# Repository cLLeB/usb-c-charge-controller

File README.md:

# ESP32-C3 smart USB-C charge controller

A small adapter that sits between a USB-C charger and a phone and stops charging at a battery level you choose, for example 80 %, then starts again at a lower one, for example 40 %. The phone reports its battery level over Wi-Fi, and the adapter does the switching. I designed the circuit and the board, wrote the firmware and the companion apps, and assembled, soldered and tested it in October 2026.

## How it works

To the charger the adapter looks like a simple 5 V device, and to the phone it looks like a simple 5 V charger. Stopping the charge is the same as pulling the plug out, so every phone already knows how to handle it.

- **Power path.** A P channel MOSFET (SI4435) switches the 5 V VBUS line, driven through a 2N7000 by the ESP32-C3. Up to 3 A at 5 V, nothing above 5 V anywhere on the board.
- **USB-C signalling.** The firmware reads the charger's CC pins to learn whether it offers basic current, 1.5 A or 3 A, then advertises the matching limit to the phone by switching one of three CC resistors.
- **Phone detection.** An analog input on the phone side CC line tells the controller whether something is plugged in, even while the output is off.
- **State.** The allowed or stopped state is kept in flash, so it survives a restart. A red LED shows the state, and the BOOT button gives "charge to 100 % once", WPS pairing and a reset.

The full circuit table, pin map and decision rules are in [DESIGN.md](DESIGN.md).

## Firmware

C++ for the Seeed XIAO ESP32-C3 in the Arduino environment ([`firmware/smart_socket/`](firmware/smart_socket)).

- Wireless control over Wi-Fi, with a web page served by the adapter and a JSON API.
- Setup over Bluetooth from the Android app, by WPS, or through a setup network.
- Firmware updates over the air, through Wi-Fi or Bluetooth, with an MD5 check before restarting into the new program.
- Each adapter answers at its own `smartsocket-xxxxxx.local` address, so several can share one network.
- Upper and lower limits, a charge timer, charging hours, a heat cut out and the last 20 charging runs.

The decision rules are mirrored in Python in [`tools/logic.py`](tools/logic.py) and covered by 62 scenario tests. [`tools/test_device.py`](tools/test_device.py) checks a real adapter feature by feature over Wi-Fi.

Before building, copy `firmware/smart_socket/secrets.example.h` to `secrets.h` and set your own update password.

## Apps

- **Android** ([`app-android/`](app-android)): finds every adapter on the network, sets one up over Bluetooth, and reports the phone's battery level in the background.
- **Windows** ([`app-windows/`](app-windows)): every adapter in one list with limits, timer, history and program upload.
- **iPhone**: two Shortcuts automations calling `http://smartsocket.local/api/battery?level=…`, described in [PHONE-SETUP.md](PHONE-SETUP.md).

## Board

Rev 0.2, 51.2 x 24 mm, two layers, made by PCBWay. The charger plugs into one end and the phone cable leaves from the other. Schematic and board are generated by scripts in [`kicad/`](kicad) and checked with ERC, DRC and a netlist comparison.

| | |
|---|---|
|  |  |
|  |  |

A 3D printed case is drafted in OpenSCAD in [`case/`](case).

## Limits of version 1

- 5 V only, up to 15 W. Laptops need 20 V and USB Power Delivery negotiation, which is a job for version 2.
- Charge only: the data wires are not connected.
- Needs a charger with a USB-C socket.

## Tools

ESP32-C3, C++, KiCad, Python, Java for Android, C# for Windows, OpenSCAD.

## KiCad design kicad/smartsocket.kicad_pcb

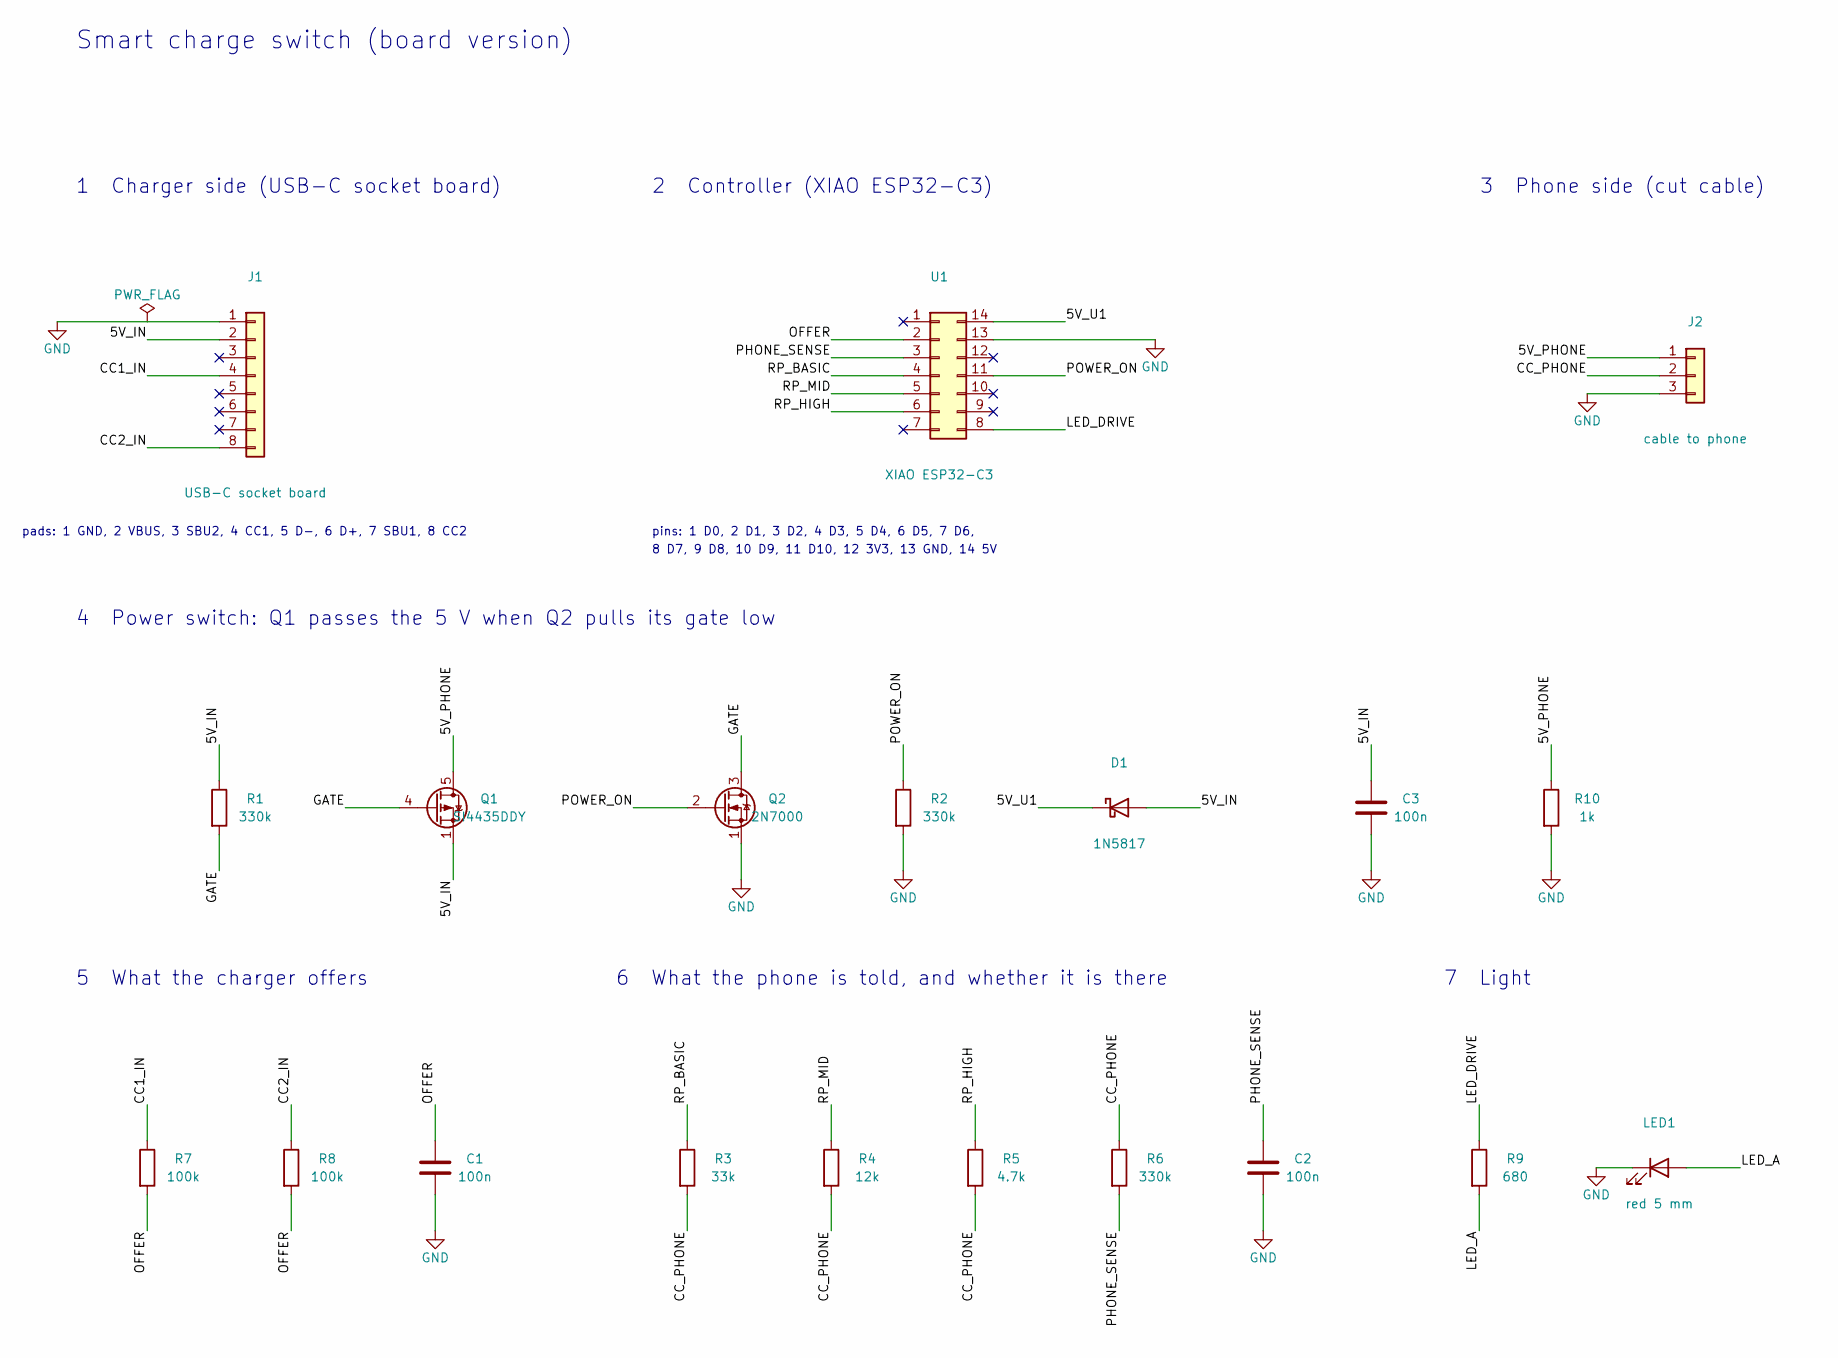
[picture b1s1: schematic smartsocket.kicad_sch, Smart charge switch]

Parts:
C1, C2, C3: 100n; C_Disc_D4.7mm_W2.5mm_P5.00mm
D1: 1N5817; D_DO-41_SOD81_P10.16mm_Horizontal
J1: USB-C socket board; PinHeader_1x08_P2.54mm_Vertical
J2: cable to phone; SolderWire-0.5sqmm_1x03_P4.6mm_D0.9mm_OD2.1mm
LED1: red 5 mm; LED_D5.0mm
Q1: SI4435DDY; SOIC-8_3.9x4.9mm_P1.27mm
Q2: 2N7000; TO-92_Inline_Wide
R1, R2, R6: 330k; R_Axial_DIN0207_L6.3mm_D2.5mm_P7.62mm_Horizontal
R3: 33k; R_Axial_DIN0207_L6.3mm_D2.5mm_P7.62mm_Horizontal
R4: 12k; R_Axial_DIN0207_L6.3mm_D2.5mm_P7.62mm_Horizontal
R5: 4.7k; R_Axial_DIN0207_L6.3mm_D2.5mm_P7.62mm_Horizontal
R7, R8: 100k; R_Axial_DIN0207_L6.3mm_D2.5mm_P7.62mm_Horizontal
R9: 680; R_Axial_DIN0207_L6.3mm_D2.5mm_P7.62mm_Horizontal
R10: 1k; R_Axial_DIN0207_L6.3mm_D2.5mm_P7.62mm_Horizontal
U1: XIAO ESP32-C3; DIP-14_W7.62mm

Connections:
/5V_IN: C3.1, D1.2 (A), J1.2, Q1.1 (S), Q1.2 (S), Q1.3 (S), R1.1
/5V_PHONE: J2.1, Q1.5 (D), Q1.6 (D), Q1.7 (D), Q1.8 (D), R10.1
/5V_U1: D1.1 (K), U1.14
/CC1_IN: J1.4, R7.1
/CC2_IN: J1.8, R8.1
/CC_PHONE: J2.2, R3.2, R4.2, R5.2, R6.1
/GATE: Q1.4 (G), Q2.3 (D), R1.2
/LED_A: LED1.2 (A), R9.2
/LED_DRIVE: R9.1, U1.8
/OFFER: C1.1, R7.2, R8.2, U1.2
/PHONE_SENSE: C2.1, R6.2, U1.3
/POWER_ON: Q2.2 (G), R2.1, U1.11
/RP_BASIC: R3.1, U1.4
/RP_HIGH: R5.1, U1.6
/RP_MID: R4.1, U1.5
GND: C1.2, C2.2, C3.2, J1.1, J2.3, LED1.1 (K), Q2.1 (S), R2.2, R10.2, U1.13

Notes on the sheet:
Smart charge switch (board version)
1 Charger side (USB-C socket board)
pads: 1 GND, 2 VBUS, 3 SBU2, 4 CC1, 5 D-, 6 D+, 7 SBU1, 8 CC2
2 Controller (XIAO ESP32-C3)
pins: 1 D0, 2 D1, 3 D2, 4 D3, 5 D4, 6 D5, 7 D6,
8 D7, 9 D8, 10 D9, 11 D10, 12 3V3, 13 GND, 14 5V
3 Phone side (cut cable)
4 Power switch: Q1 passes the 5 V when Q2 pulls its gate low
5 What the charger offers
6 What the phone is told, and whether it is there
7 Light

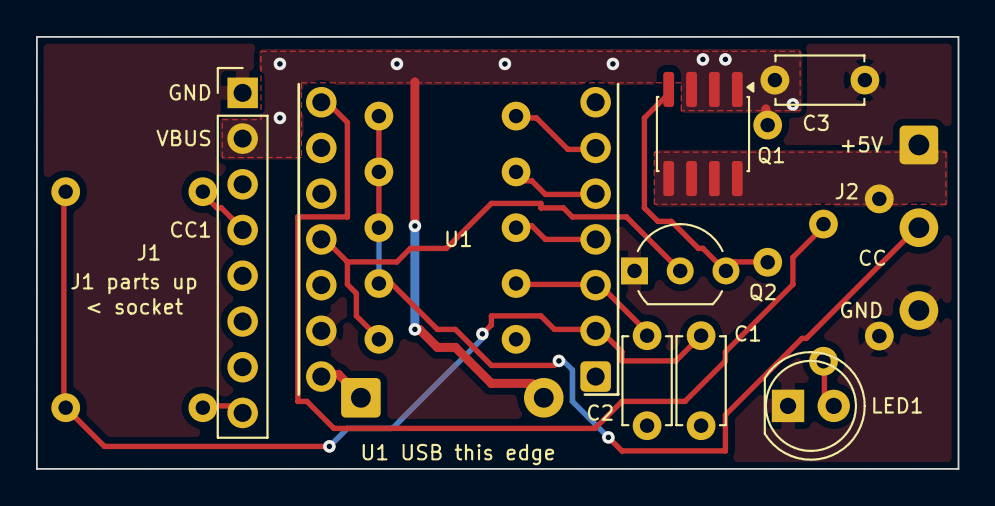
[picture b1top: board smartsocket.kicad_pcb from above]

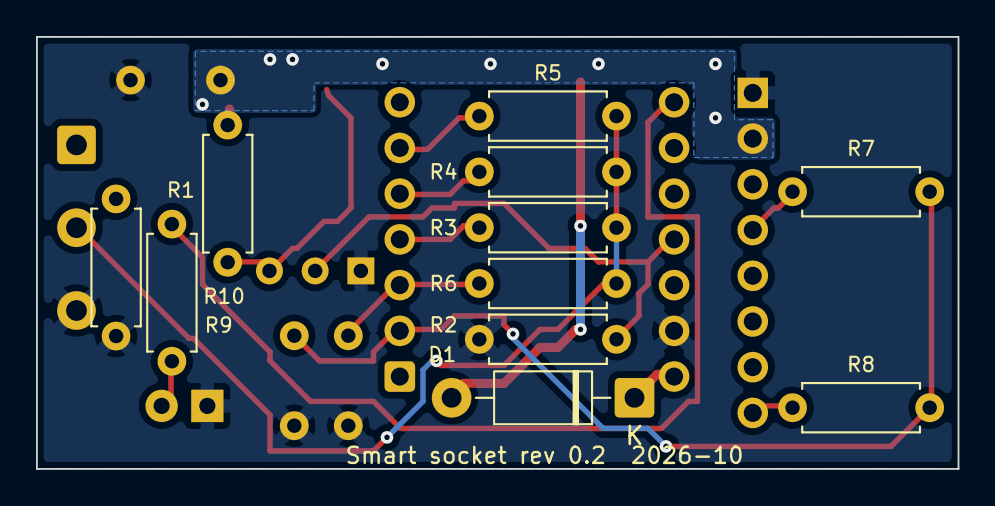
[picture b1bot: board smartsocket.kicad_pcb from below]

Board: 2 copper layers, 51.2 x 24.0 mm, 20 parts (11 on the bottom side), 16 nets.

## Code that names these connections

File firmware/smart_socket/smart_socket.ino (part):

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
// ---------------------------------------------------------------- Pins (GPIO numbers)
const int PIN_SRC_SENSE = 3;   // D1: charger CC1 + CC2 through 100 k each, halved
const int PIN_PHONE_SENSE = 4; // D2: phone CC through 100 k
const int PIN_RP_BASIC = 5;    // D3: 33 k to phone CC
const int PIN_RP_MID = 6;      // D4: 12 k to phone CC
const int PIN_RP_HIGH = 7;     // D5: 4.7 k to phone CC
const int PIN_LED = 20;        // D7
const int PIN_POWER = 10;      // D10: high turns the 5 V switch on
const int PIN_BUTTON = 9;      // BOOT button on the board, low when pressed
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// Exactly one of the three resistors is driven high; the other two pins float.
void applyRp(int ma) {
  if (ma == appliedMa) return;
  int pin = (ma == HIGH_MA) ? PIN_RP_HIGH : (ma == MID_MA) ? PIN_RP_MID : PIN_RP_BASIC;
  const int pins[] = {PIN_RP_BASIC, PIN_RP_MID, PIN_RP_HIGH};
  pinMode(pin, OUTPUT);
  digitalWrite(pin, HIGH);
  for (int p : pins) {
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    offerMv = offerMv < 0 ? mv : (offerMv * 7 + mv) / 8;
    srcMa = sourceMa(offerMv);
  }
  bool present = phonePresent(readMv(PIN_PHONE_SENSE), appliedMa);
  logicStep(now, present, currentLimited ? BASIC_MA : srcMa, minuteOfDay(), tempC);
  applyOutputs();
  historyPass(now);
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  j += ",\"temp_c\":" + String(tempC, 1) + ",\"hot\":" + String(st.hot ? "true" : "false");
  j += ",\"led\":" + String(cfg.led);
  j += ",\"src_ma\":" + String(srcMa) + ",\"out_ma\":" + String(st.outMa);
  j += ",\"offer_mv\":" + String(offerMv) + ",\"phone_mv\":" + String(readMv(PIN_PHONE_SENSE));
  j += ",\"reset\":\"" + String(resetWhy()) + "\",\"boots\":" + String(bootCount) + ",\"ble_links\":" + String(bleServer ? (int)bleServer->getConnectedCount() : 0);
  j += ",\"charge_s\":" + String(chargeSince < 0 ? -1 : (long)((now - chargeSince) / 1000));
  j += ",\"limited\":" + String(currentLimited ? "true" : "false");
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                FW_VERSION, devId.c_str(), devName.c_str(), (long)(now / 1000),
                connected ? WiFi.SSID().c_str() : (setupMode ? setupApName.c_str() : (currentSsid.length() ? currentSsid.c_str() : "searching")),
                (connected ? WiFi.localIP() : WiFi.softAPIP()).toString().c_str(), wifiFailReason, wifiSeenRssi,
                setupMode, wpsActive, netCount, tempC, readMv(PIN_SRC_SENSE), readMv(PIN_PHONE_SENSE), srcMa, currentLimited,
                st.presentSince >= 0, st.vbus, REASON_NAMES[st.reason], st.outMa, st.allow, modeName(cfg.mode), st.level,
                minuteOfDay());
}
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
